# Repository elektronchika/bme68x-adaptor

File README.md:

# bme68x-adaptor

Bosch Sensortec BME680 and BME688 simple adaptor board

https://www.bosch-sensortec.com/products/environmental-sensors/gas-sensors/bme680/

https://www.bosch-sensortec.com/products/environmental-sensors/gas-sensors/bme688/

Top View

Bottom View

If you like my work, consider to buy me a coffee

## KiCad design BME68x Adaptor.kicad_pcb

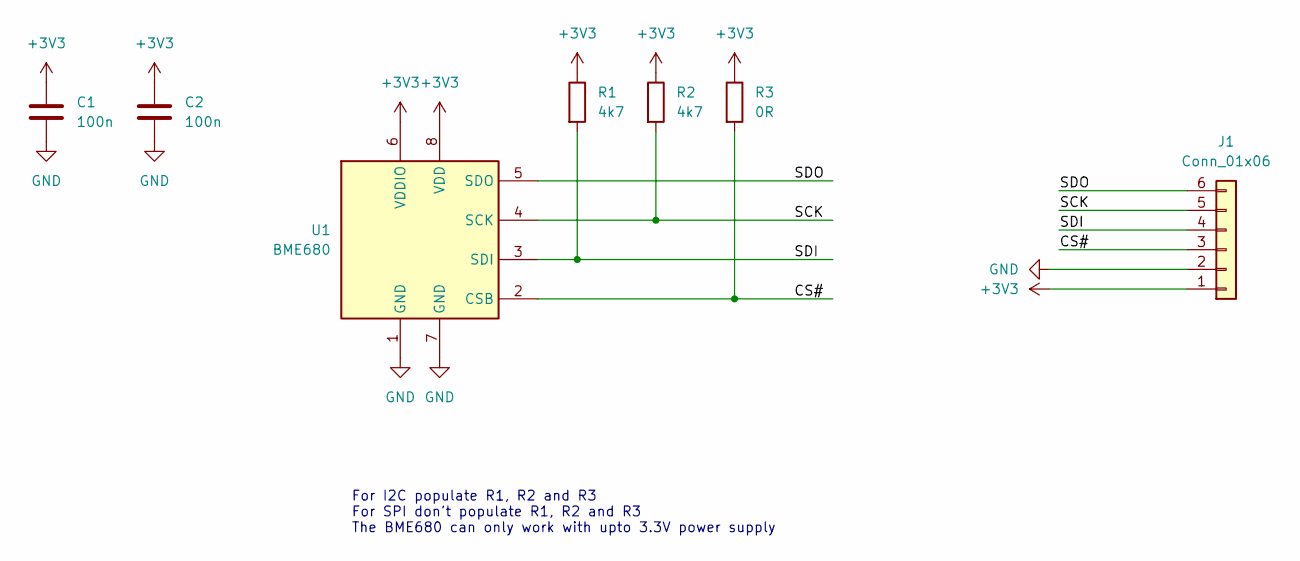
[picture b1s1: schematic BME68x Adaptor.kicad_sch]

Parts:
C1, C2: 100n; C_0603_1608Metric_Pad1.08x0.95mm_HandSolder
J1: Conn_01x06; PinHeader_1x06_P2.54mm_Horizontal
R1, R2: 4k7; R_0603_1608Metric_Pad0.98x0.95mm_HandSolder
R3: 0R; R_0603_1608Metric_Pad0.98x0.95mm_HandSolder
U1: BME680; Bosch_LGA-8_3x3mm_P0.8mm_ClockwisePinNumbering

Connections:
+3V3: C1.1, C2.1, J1.1, R1.1, R2.1, R3.1, U1.6 (VDDIO), U1.8 (VDD)
/CS#: J1.3, R3.2, U1.2 (CSB)
/SCK: J1.5, R2.2, U1.4 (SCK)
/SDI: J1.4, R1.2, U1.3 (SDI)
/SDO: J1.6, U1.5 (SDO)
GND: C1.2, C2.2, J1.2, U1.1 (GND), U1.7 (GND)

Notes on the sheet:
For I2C populate R1, R2 and R3 For SPI don't populate R1, R2 and R3 The BME680 can only work with upto 3.3V power supply

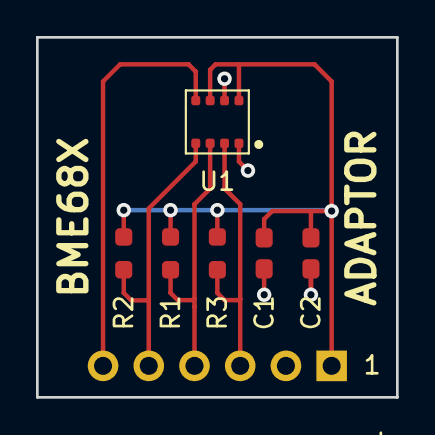
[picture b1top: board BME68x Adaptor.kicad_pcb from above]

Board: 2 copper layers, 20.0 x 20.0 mm, 7 parts (0 on the bottom side), 6 nets.

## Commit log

2022-04-04 initial commit. schematic done.
    pcb layout needs to be redesigned
2022-04-04 added readme
2022-04-05 layout finished
2022-04-05 Silkscreen improved
2022-04-05 Added gerber files
2022-04-21 added ibom
2024-09-19 added screenshots
2024-09-19 swapped top and bottom views
